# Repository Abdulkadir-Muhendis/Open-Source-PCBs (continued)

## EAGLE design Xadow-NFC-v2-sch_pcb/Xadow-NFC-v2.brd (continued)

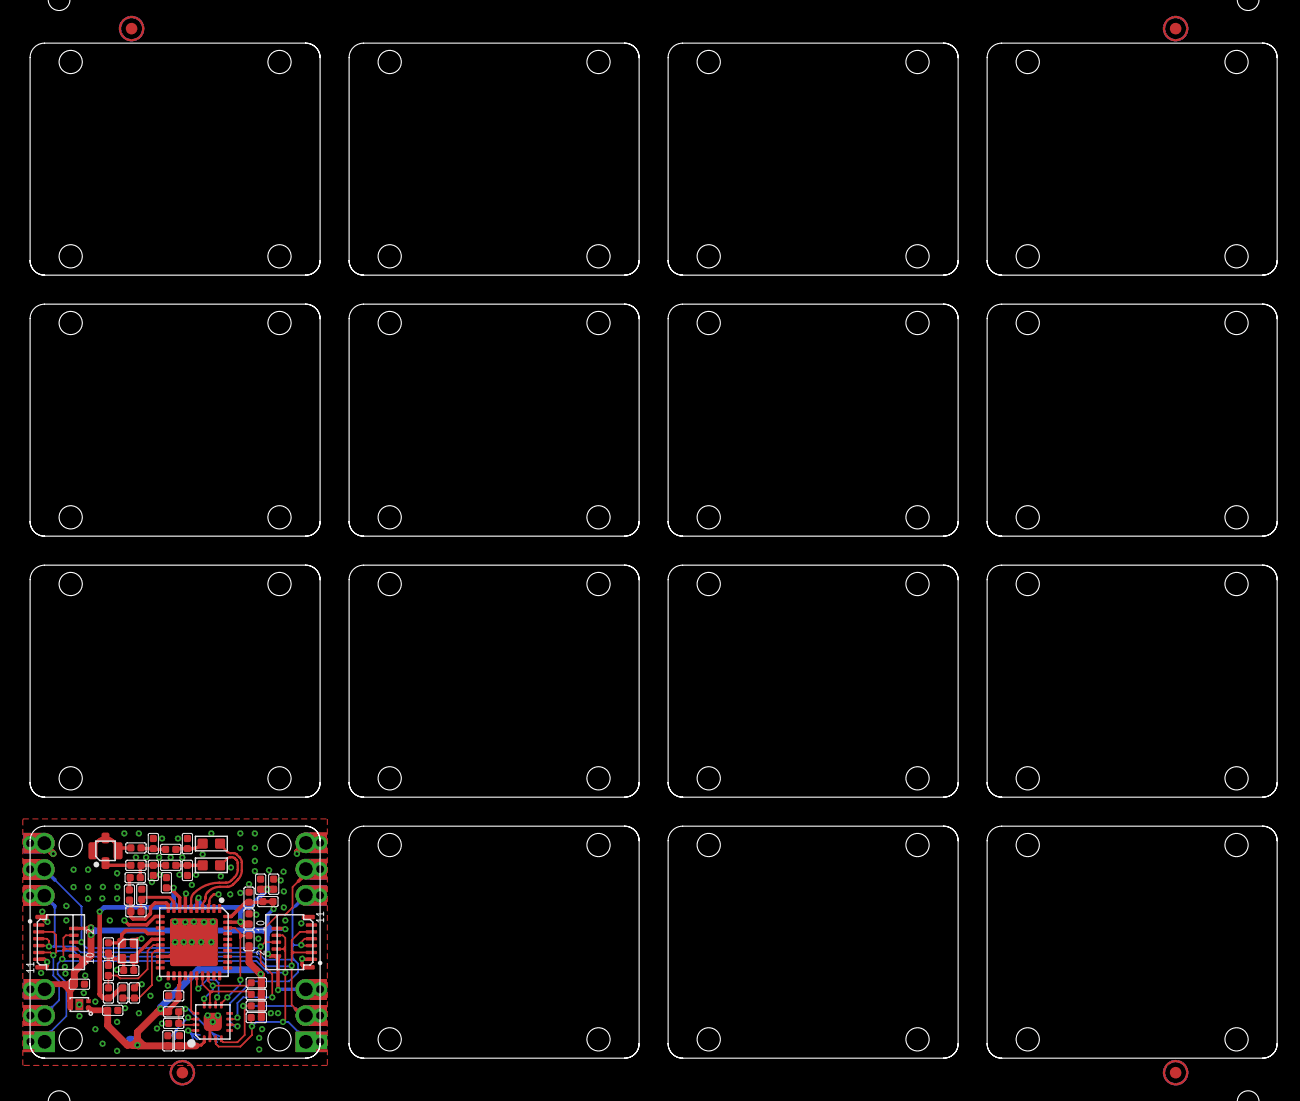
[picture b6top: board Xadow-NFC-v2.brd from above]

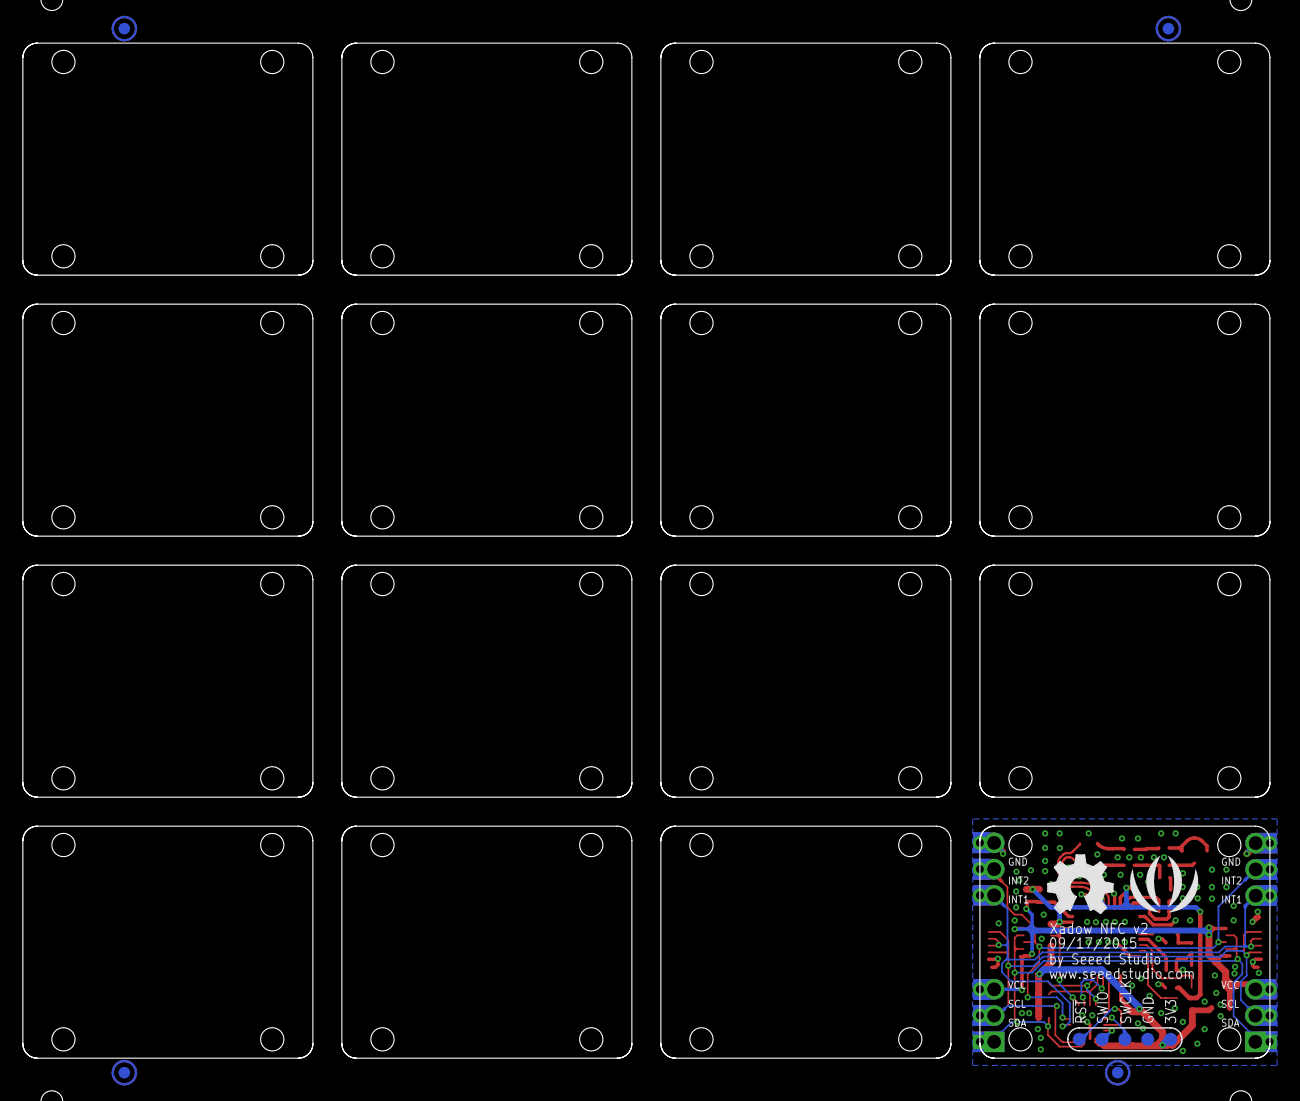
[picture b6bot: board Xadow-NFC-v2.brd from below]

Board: 2 copper layers, 109.2 x 88.9 mm, 62 parts (7 on the bottom side), 31 nets.

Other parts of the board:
U$27: OSHW_FILLX200_NOTEXT
U$29: SEEED-SILK-280*268MIL

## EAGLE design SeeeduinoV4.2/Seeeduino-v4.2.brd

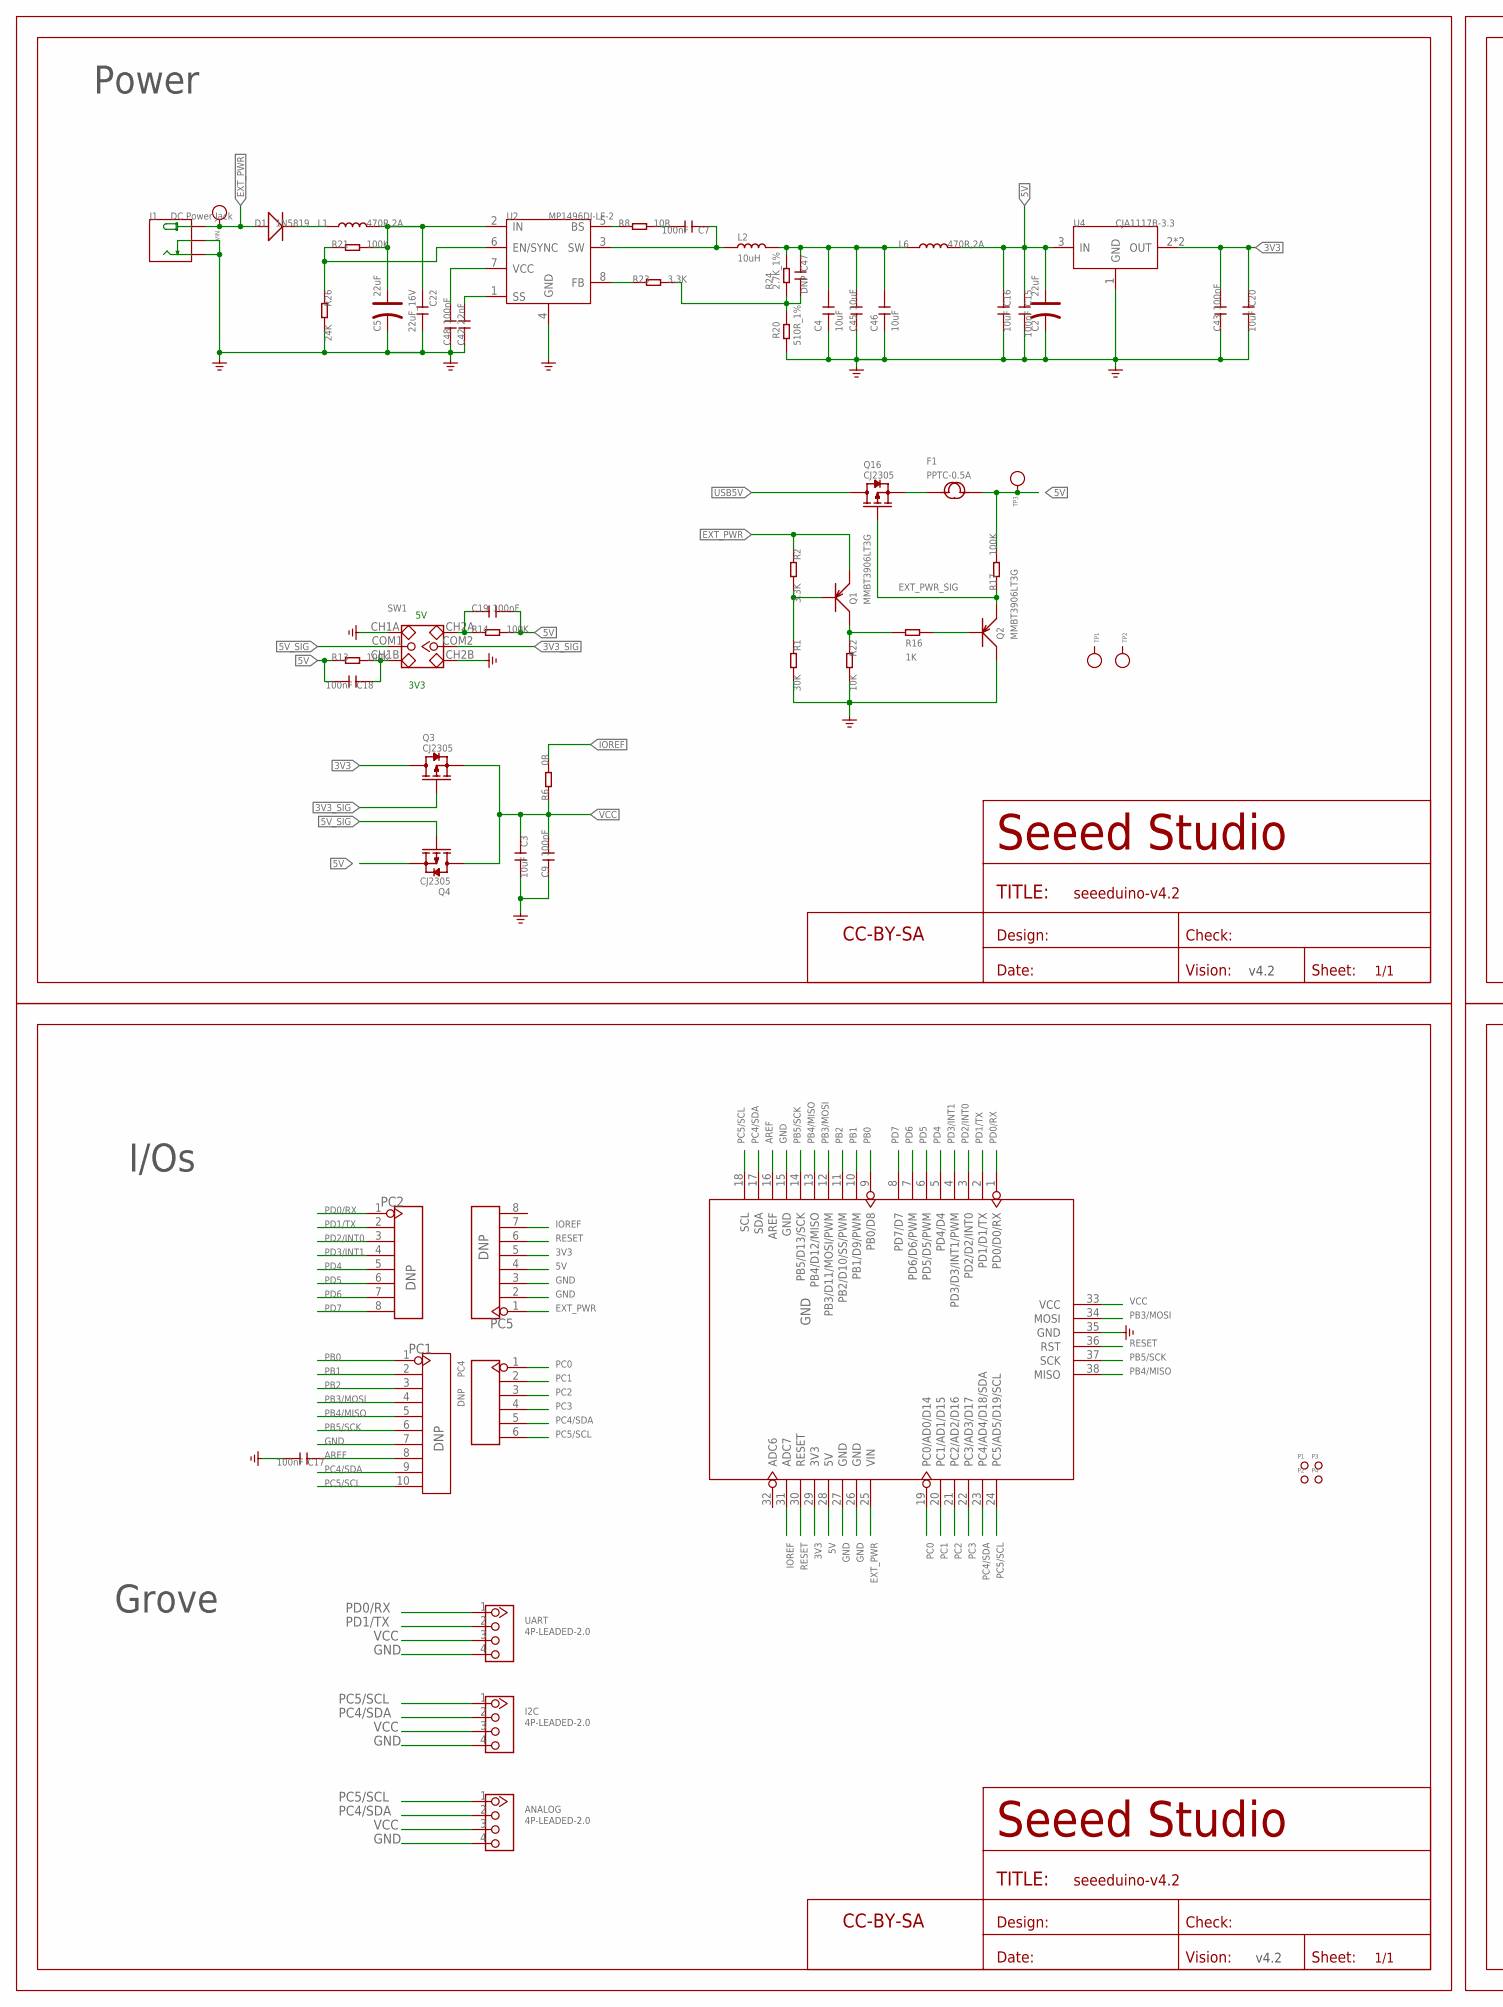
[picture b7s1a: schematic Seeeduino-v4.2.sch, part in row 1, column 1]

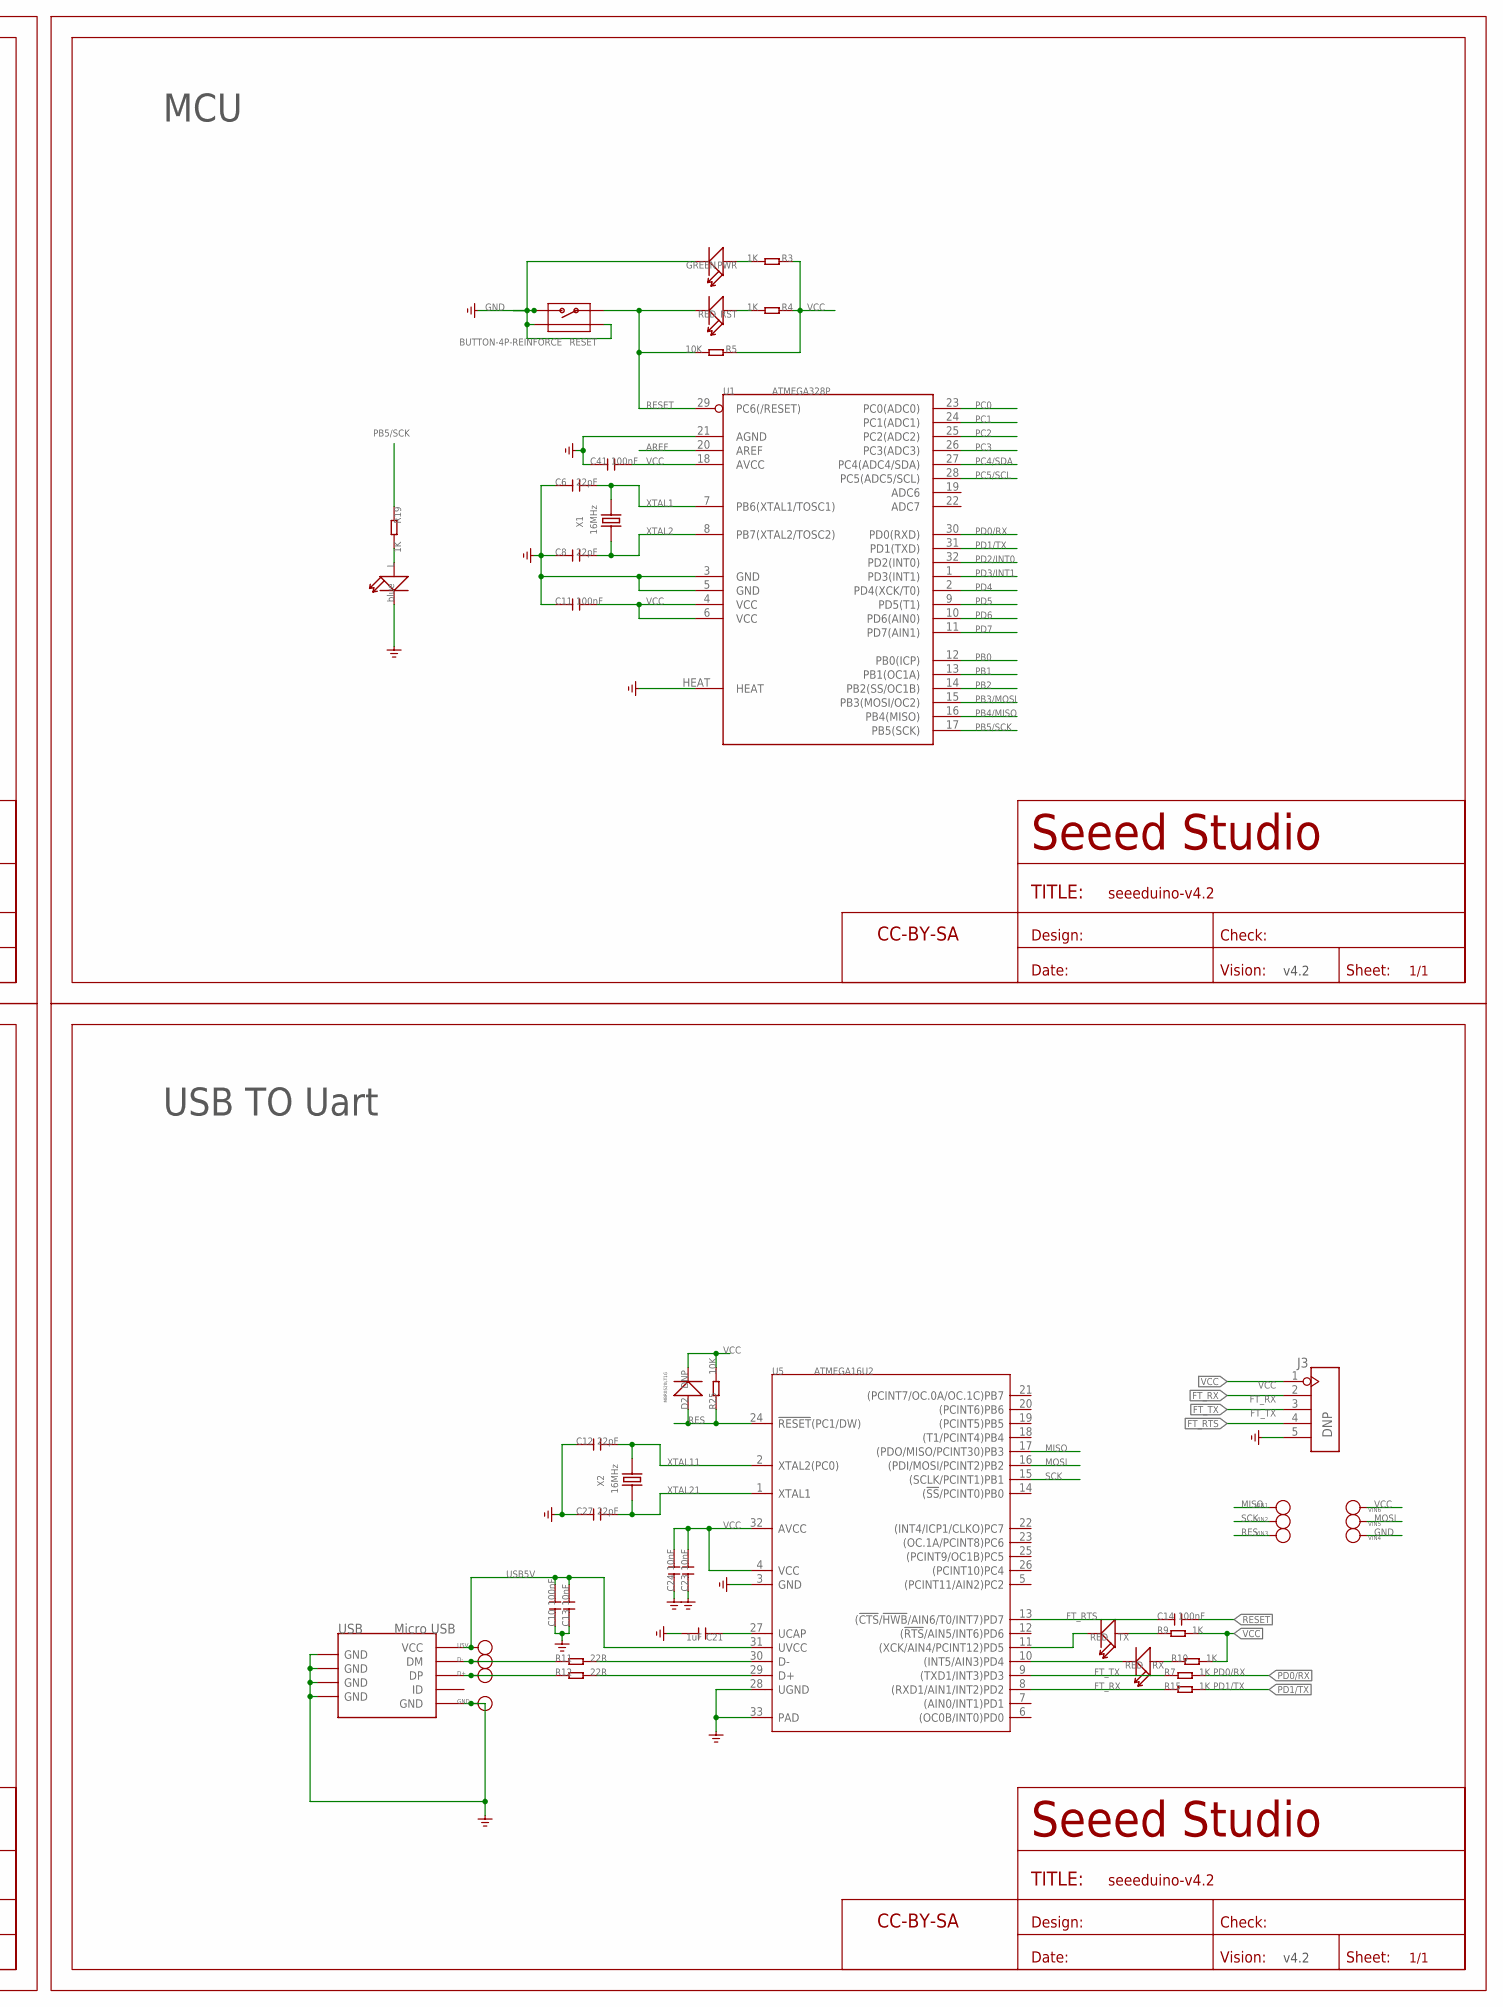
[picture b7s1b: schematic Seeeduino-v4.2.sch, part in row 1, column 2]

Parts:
ANALOG: 4P-LEADED-2.0
C2, C5: 22uF; ELECTRO-SMD-B-4.8MM
C3, C4, C16, C20, C45: 10uF; C0805
C6, C8, C12, C27: 22pF; C0603
C7, C9, C10, C11, C14, C15, C17, C18, C19, C41, C43, C48: 100nF; C0603
C13, C23, C24: 10nF; C0603
C21: 1uF; C0603
C22: 22uF_16V; C1206
C42: 22nF; C0603
C46: 10uF; C1206
C47: DNP; C0603
D1: 1N5819; D2010
D2: DNP; SOD123
D+: PAD-TEST-POINT'4545'; TP_4545
D-: PAD-TEST-POINT'4545'; TP_4545
F1: PPTC-0.5A; F1206
GND: PAD-TEST-POINT'4545'; TP_4545
I2C: 4P-LEADED-2.0
J1: DC Power Jack; DC-404
J3: DNP; 5P-2.54
L: blue; LED-0603
L1, L6: 470R,2A; L0805
L2: 10uH; L5040S
P1, P2, P3, P4: PAD-MARK; ROUND-MARK-1.0
PC1: DNP; 10P-2.54
PC2, PC5: DNP; 8P-2.54
PC4: DNP; 6P-2.54-65/35MIL
PWR: GREEN; LED-0603
Q1, Q2: MMBT3906LT3G; SOT23
Q3, Q4, Q16: CJ2305; SOT23
R1: 30K; R0603
R2, R23: 3.3K; R0603
R3, R4, R7, R9, R10, R15, R16, R19: 1K; R0603
R5, R22, R25: 10K; R0603
R6: 0R; R0603
R8: 10R; R0603
R11, R12: 22R; R0603
R13, R14, R17, R21: 100K; R0603
R20: 510R_1%; R0603
R24: 2.7K_1%; R0603
R26: 24K; R0603
RESET: BUTTON-4P-REINFORCE; 4P-SMD-7X3.5X3.5H
RST: RED; LED-0603
RX: RED; LED-0603
SW1: SWITCH-2CH-6P-2.54; 6P-SMD-2CH-2.54-3.5X7.2
TP1, TP2, TP3: PAD-TEST-POINT'4545'; TP_4545
TX: RED; LED-0603
U1: ATMEGA328P; MLF32X
U2: MP1496DJ-LF-2; TSOT23-8
U3: ARDUINO-38P
U4: CJA1117B-3.3; SOT-89
U5: ATMEGA16U2; QFN32
U5V: PAD-TEST-POINT'4545'; TP_4545
U$1, U$6, U$8, U$23: SEEEDSTUDIO-OPEN-SCH-FRAME; SEEEDSTUDIO-PCB-FRAME
UART: 4P-LEADED-2.0
USB: Micro USB; MICRO-USB
VIN, VIN1, VIN2, VIN3, VIN4, VIN5, VIN6: PAD-TEST-POINT'4545'; TP_4545
X1, X2: 16MHz; 2P-SMD-5X3.2

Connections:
3V3: C20.1, C43.2, PC5.5, Q3.3 (D), U3.29 (3V3), U4.2 (OUT), U4.4 (OUT)
3V3_SIG: Q3.1 (G), SW1.COM2
5V: C2.+, C15.1, C16.1, C18.2, C19.2, F1.2, L6.2, PC5.4, Q4.2 (S), R13.1, R14.2, R17.2, TP3.T, U3.28 (5V), U4.3 (IN)
5V_SIG: Q4.1 (G), SW1.COM1
AREF: C17.1, PC1.8, U1.20 (AREF), U3.16 (AREF)
D+: D+.T, R12.1, USB.3 (DP)
D-: D-.T, R11.1, USB.2 (DM)
EXT_PWR: D1.+, J1.+, PC5.1, Q1.2 (E), R2.1, U3.25 (VIN), VIN.T
EXT_PWR_SIG: Q2.2 (E), Q16.1 (G), R17.1
FT_RTS: C14.1, J3.4, U5.13 ((!CTS!/!HWB!/AIN6/T0/INT7)PD7)
FT_RX: J3.2, R15.1, U5.8 ((RXD1/AIN1/INT2)PD2)
FT_TX: J3.3, R7.1, U5.9 ((TXD1/INT3)PD3)
GND: ANALOG.4, C2.-, C3.2, C4.1, C5.-, C6.1, C8.1, C9.1, C10.1, C11.1, C12.1, C13.1, C15.2, C16.2, C17.2, C20.2, C21.2, C22.2, C23.1, C24.1, C27.1, C41.1, C42.1, C43.1, C45.1, C46.1, C48.1, GND.T, I2C.4, J1.-, J1.CDN, J3.5, L.-, PC1.7, PC5.2, PC5.3, PWR.-, Q2.3 (C), R1.2, R20.1, R22.2, R26.2, RESET.2, RESET.S1, RESET.S2, SW1.CH1A, SW1.CH2B, U1.3 (GND), U1.5 (GND), U1.21 (AGND), U1.HEAT, U2.4 (GND), U3.15 (GND), U3.26 (GND), U3.27 (GND), U3.35 (GND), U4.1 (GND), U5.3 (GND), U5.28 (UGND), U5.33 (PAD), UART.4, USB.5 (GND), USB.S1 (GND), USB.S2 (GND), USB.S3 (GND), USB.S4 (GND), USB.S5 (GND), USB.S6 (GND), VIN4.T
IOREF: PC5.7, R6.2, U3.31 (ADC7)
MISO: U5.17 ((PDO/MISO/PCINT30)PB3), VIN1.T
MOSI: U5.16 ((PDI/MOSI/PCINT2)PB2), VIN5.T
unnamed: TX.-, U5.11 ((XCK/AIN4/PCINT12)PD5)
unnamed: R21.1, R26.1, U2.6 (EN/SYNC)
unnamed: L.+, R19.2
unnamed: Q1.1 (B), R1.1, R2.2
unnamed: R11.2, U5.30 (D-)
unnamed: PWR.+, R3.2
unnamed: Q2.1 (B), R16.2
unnamed: Q1.3 (C), R16.1, R22.1
unnamed: D1.-, L1.1
unnamed: C18.1, R13.2, SW1.CH1B
unnamed: R10.1, RX.+
unnamed: R12.2, U5.29 (D+)
unnamed: RX.-, U5.10 ((INT5/AIN3)PD4)
unnamed: C19.1, R14.1, SW1.CH2A
unnamed: R4.2, RST.+
unnamed: C21.1, U5.27 (UCAP)
unnamed: C48.2, U2.7 (VCC)
unnamed: C42.2, U2.1 (SS)
unnamed: R8.1, U2.5 (BS)
unnamed: C7.1, L2.1, U2.3 (SW)
unnamed: C7.2, R8.2
unnamed: R23.1, U2.8 (FB)
unnamed: C47.2, R20.2, R23.2, R24.2
unnamed: R9.1, TX.+
OUT1: C4.2, C45.2, C46.2, C47.1, L2.2, L6.1, R24.1
P5V: F1.1, Q16.2 (S)
PB0: PC1.1, U1.12 (PB0(ICP)), U3.9 (PB0/D8)
PB1: PC1.2, U1.13 (PB1(OC1A)), U3.10 (PB1/D9/PWM)
PB2: PC1.3, U1.14 (PB2(SS/OC1B)), U3.11 (PB2/D10/SS/PWM)
PB3/MOSI: PC1.4, U1.15 (PB3(MOSI/OC2)), U3.12 (PB3/D11/MOSI/PWM), U3.34 (MOSI)
PB4/MISO: PC1.5, U1.16 (PB4(MISO)), U3.13 (PB4/D12/MISO), U3.38 (MISO)
PB5/SCK: PC1.6, R19.1, U1.17 (PB5(SCK)), U3.14 (PB5/D13/SCK), U3.37 (SCK)
PC0: PC4.1, U1.23 (PC0(ADC0)), U3.19 (PC0/AD0/D14)
PC1: PC4.2, U1.24 (PC1(ADC1)), U3.20 (PC1/AD1/D15)
PC2: PC4.3, U1.25 (PC2(ADC2)), U3.21 (PC2/AD2/D16)
PC3: PC4.4, U1.26 (PC3(ADC3)), U3.22 (PC3/AD3/D17)
PC4/SDA: ANALOG.2, I2C.2, PC1.9, PC4.5, U1.27 (PC4(ADC4/SDA)), U3.17 (SDA), U3.23 (PC4/AD4/D18/SDA)
PC5/SCL: ANALOG.1, I2C.1, PC1.10, PC4.6, U1.28 (PC5(ADC5/SCL)), U3.18 (SCL), U3.24 (PC5/AD5/D19/SCL)
PD0/RX: PC2.1, R7.2, U1.30 (PD0(RXD)), U3.1 (PD0/D0/RX), UART.1
PD1/TX: PC2.2, R15.2, U1.31 (PD1(TXD)), U3.2 (PD1/D1/TX), UART.2
PD2/INT0: PC2.3, U1.32 (PD2(INT0)), U3.3 (PD2/D2/INT0)
PD3/INT1: PC2.4, U1.1 (PD3(INT1)), U3.4 (PD3/D3/INT1/PWM)
PD4: PC2.5, U1.2 (PD4(XCK/T0)), U3.5 (PD4/D4)
PD5: PC2.6, U1.9 (PD5(T1)), U3.6 (PD5/D5/PWM)
PD6: PC2.7, U1.10 (PD6(AIN0)), U3.7 (PD6/D6/PWM)
PD7: PC2.8, U1.11 (PD7(AIN1)), U3.8 (PD7/D7)
PWR_IN: C5.+, C22.1, L1.2, R21.2, U2.2 (IN)
RES: D2.+, R25.1, U5.24 (!RESET!(PC1/DW)), VIN3.T
RESET: C14.2, PC5.6, R5.2, RESET.1, RST.-, U1.29 (PC6(/RESET)), U3.30 (RESET), U3.36 (RST)
SCK: U5.15 ((SCLK/PCINT1)PB1), VIN2.T
USB5V: C10.2, C13.2, Q16.3 (D), U5.31 (UVCC), U5V.T, USB.1 (VCC)
VCC: ANALOG.3, C3.1, C9.2, C11.2, C23.2, C24.2, C41.2, D2.-, I2C.3, J3.1, Q3.2 (S), Q4.3 (D), R3.1, R4.1, R5.1, R6.1, R9.2, R10.2, R25.2, U1.4 (VCC), U1.6 (VCC), U1.18 (AVCC), U3.33 (VCC), U5.4 (VCC), U5.32 (AVCC), UART.3, VIN6.T
XTAL1: C6.2, U1.7 (PB6(XTAL1/TOSC1)), X1.2
XTAL2: C8.2, U1.8 (PB7(XTAL2/TOSC2)), X1.1
XTAL11: C12.2, U5.2 (XTAL2(PC0)), X2.2
XTAL21: C27.2, U5.1 (XTAL1), X2.1

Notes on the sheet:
I/Os
Grove
USB TO Uart
MCU
Power
MBR0520LT1G
3V3
v4.2

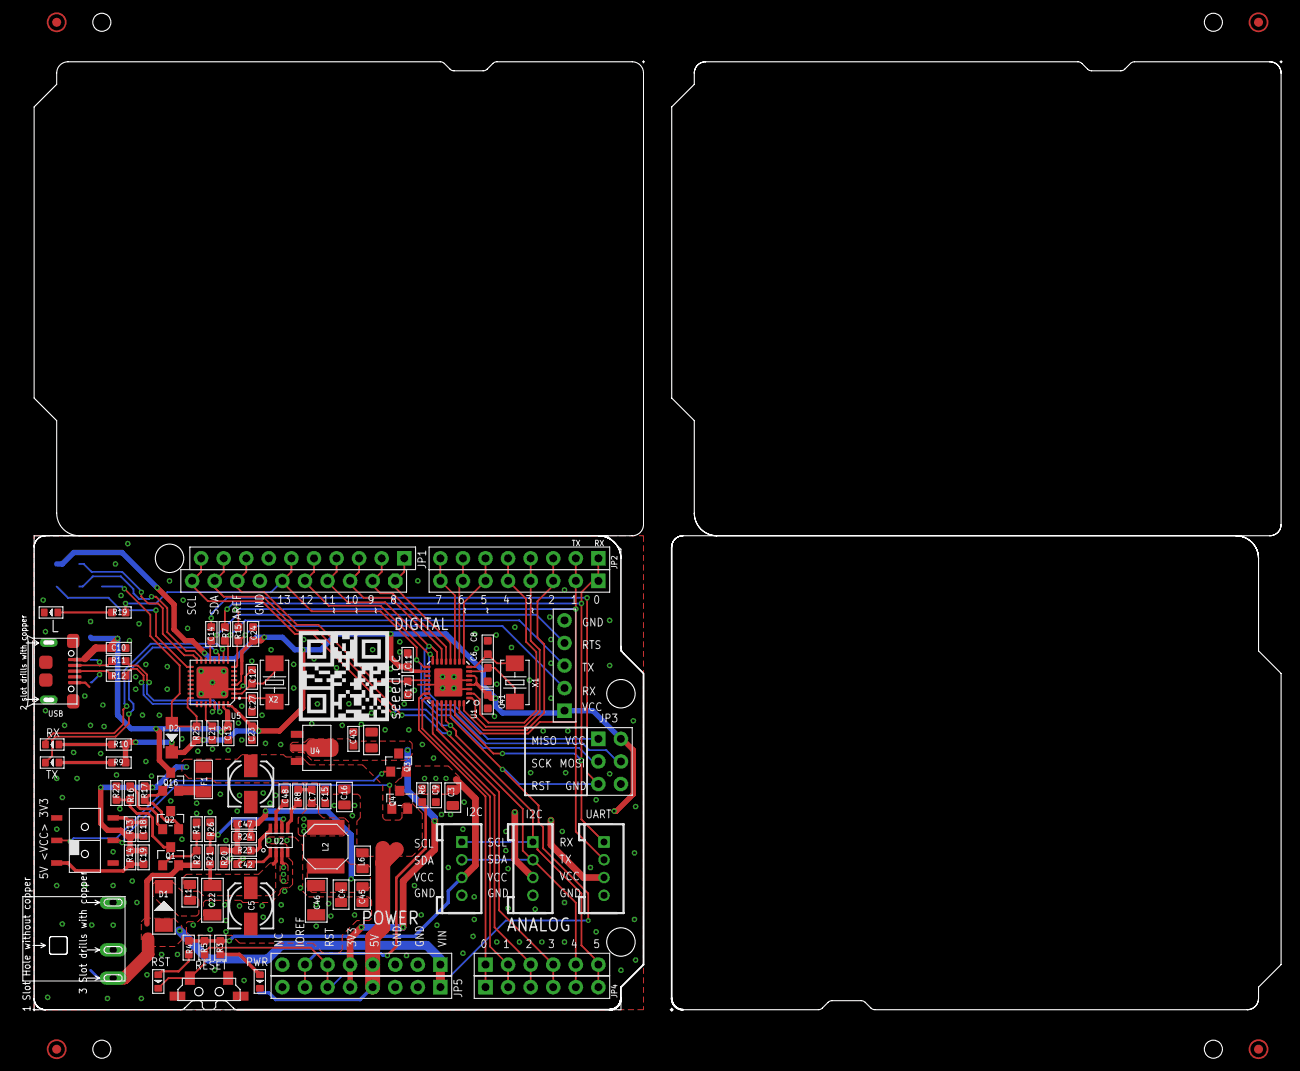
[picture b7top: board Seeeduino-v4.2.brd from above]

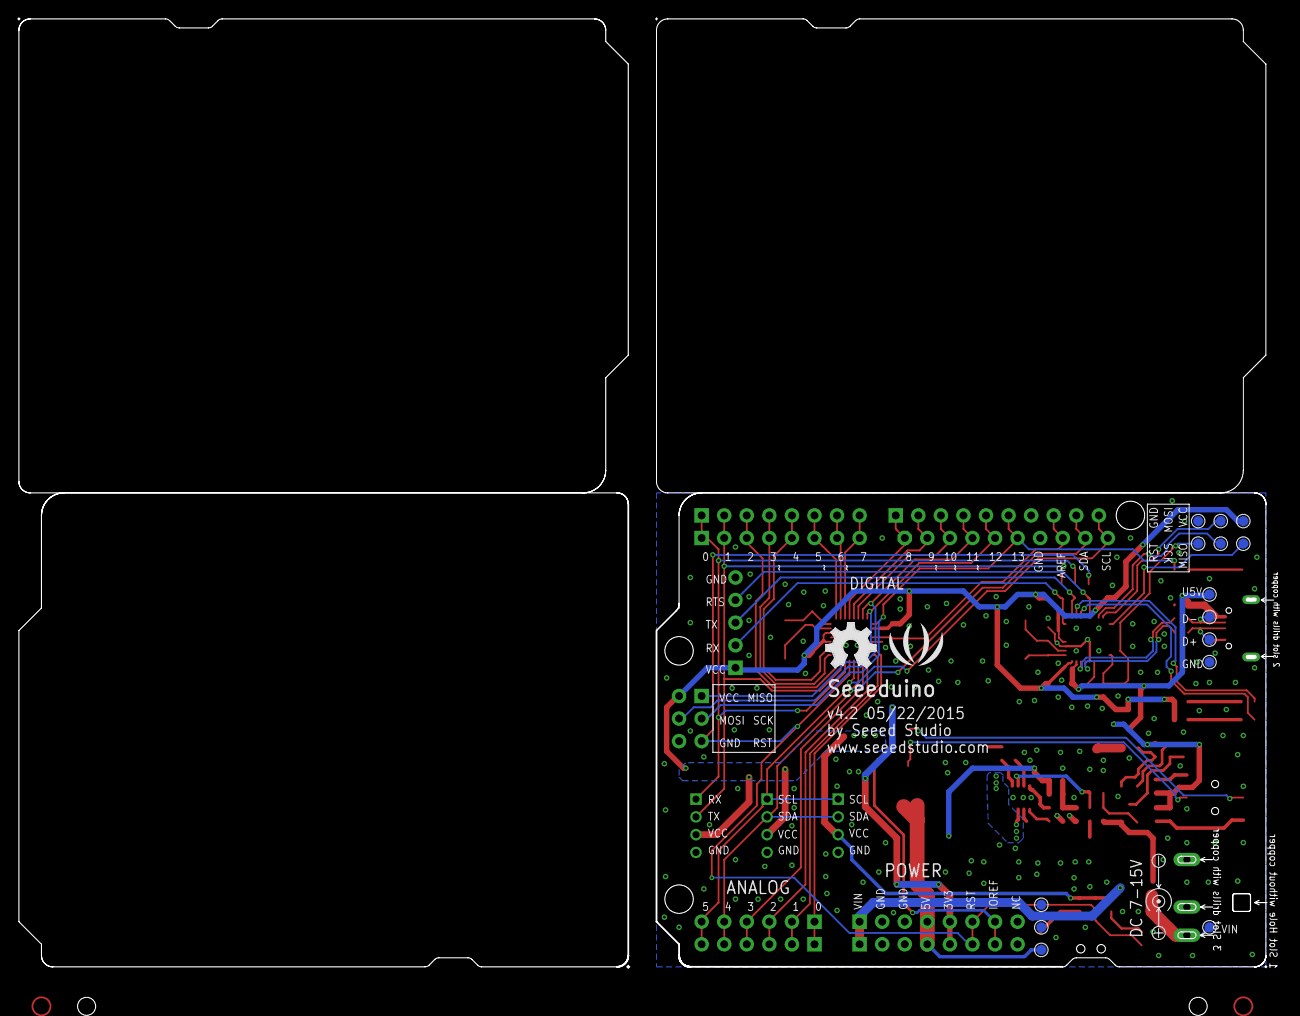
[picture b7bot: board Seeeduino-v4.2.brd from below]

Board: 2 copper layers, 141.4 x 106.9 mm, 116 parts (16 on the bottom side), 72 nets.

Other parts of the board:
U$2: SEEED-MASK-280*268MIL
U$4: LOGO_SILK
U$5: OSHW_FILLX200_NOTEXT
